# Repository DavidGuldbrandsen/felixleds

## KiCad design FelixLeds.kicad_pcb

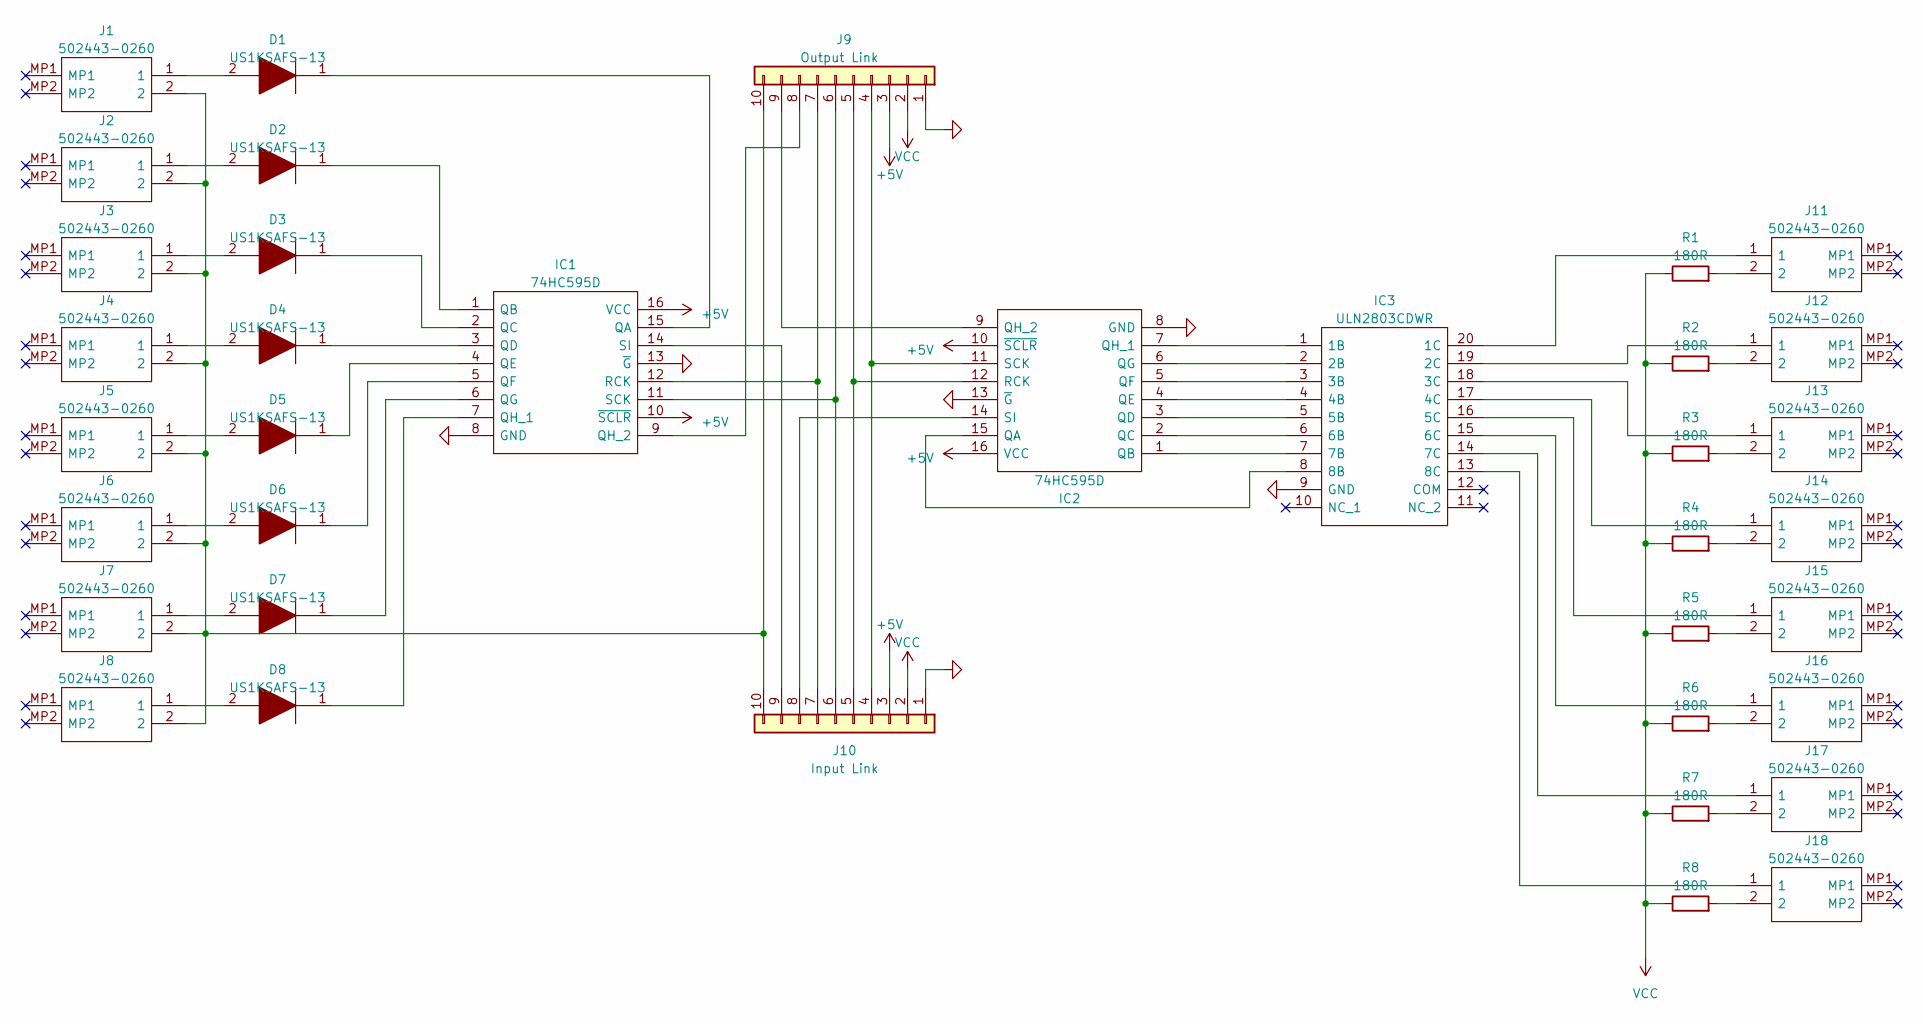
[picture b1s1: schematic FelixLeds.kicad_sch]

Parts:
D1, D2, D3, D4, D5, D6, D7, D8: US1KSAFS-13; SODFL4625X120N; Mouser Part Number 621-US1KSAFS-13
IC1, IC2: 74HC595D; SOIC127P600X175-16N; Mouser Part Number 757-74HC595D
IC3: ULN2803CDWR; SOIC127P1030X265-20N; Mouser Part Number 595-ULN2803CDWR
J1, J2, J3, J4, J5, J6, J7, J8, J11, J12, J13, J14, J15, J16, J17, J18: 502443-0260; 5024430260; Mouser Part Number 538-502443-0260
J9: Output Link; PinHeader_1x10_P2.54mm_Vertical
J10: Input Link; PinHeader_1x10_P2.54mm_Vertical
R1, R2, R3, R4, R5, R6, R7, R8: 180R; R_0603_1608Metric

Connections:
+5V: IC1.10 (~SCLR), IC1.16 (VCC), IC2.10 (~SCLR), IC2.16 (VCC), J9.3, J10.3
GND: IC1.8 (GND), IC1.13 (~G), IC2.8 (GND), IC2.13 (~G), IC3.9 (GND), J9.1, J10.1
unnamed: D1.2, J1.1
unnamed: D2.2, J2.1
unnamed: D3.2, J3.1
unnamed: D4.2, J4.1
unnamed: D5.2, J5.1
unnamed: D6.2, J6.1
unnamed: D7.2, J7.1
unnamed: D8.2, J8.1
unnamed: D1.1, IC1.15 (QA)
unnamed: D2.1, IC1.1 (QB)
unnamed: D3.1, IC1.2 (QC)
unnamed: D4.1, IC1.3 (QD)
unnamed: D5.1, IC1.4 (QE)
unnamed: D6.1, IC1.5 (QF)
unnamed: D7.1, IC1.6 (QG)
unnamed: D8.1, IC1.7 (QH_1)
unnamed: IC1.9 (QH_2), J9.8
unnamed: IC1.12 (RCK), J9.7, J10.7
unnamed: IC1.11 (SCK), J9.6, J10.6
unnamed: IC1.14 (SI), J10.9
unnamed: IC2.15 (QA), IC3.8 (8B)
unnamed: IC2.1 (QB), IC3.7 (7B)
unnamed: IC2.2 (QC), IC3.6 (6B)
unnamed: IC2.3 (QD), IC3.5 (5B)
unnamed: IC2.4 (QE), IC3.4 (4B)
unnamed: IC2.5 (QF), IC3.3 (3B)
unnamed: IC2.6 (QG), IC3.2 (2B)
unnamed: IC2.7 (QH_1), IC3.1 (1B)
unnamed: IC2.9 (QH_2), J9.9
unnamed: IC2.12 (RCK), J9.5, J10.5
unnamed: IC2.11 (SCK), J9.4, J10.4
unnamed: IC2.14 (SI), J10.8
unnamed: IC3.20 (1C), J11.1
unnamed: IC3.19 (2C), J12.1
unnamed: IC3.18 (3C), J13.1
unnamed: IC3.17 (4C), J14.1
unnamed: IC3.16 (5C), J15.1
unnamed: IC3.15 (6C), J16.1
unnamed: IC3.14 (7C), J17.1
unnamed: IC3.13 (8C), J18.1
unnamed: J1.2, J2.2, J3.2, J4.2, J5.2, J6.2, J7.2, J8.2, J9.10, J10.10
unnamed: J11.2, R1.2
unnamed: J12.2, R2.2
unnamed: J13.2, R3.2
unnamed: J14.2, R4.2
unnamed: J15.2, R5.2
unnamed: J16.2, R6.2
unnamed: J17.2, R7.2
unnamed: J18.2, R8.2
VCC: J9.2, J10.2, R1.1, R2.1, R3.1, R4.1, R5.1, R6.1, R7.1, R8.1

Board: 2 copper layers, 37 parts (0 on the bottom side), 52 nets, no tracks yet.
